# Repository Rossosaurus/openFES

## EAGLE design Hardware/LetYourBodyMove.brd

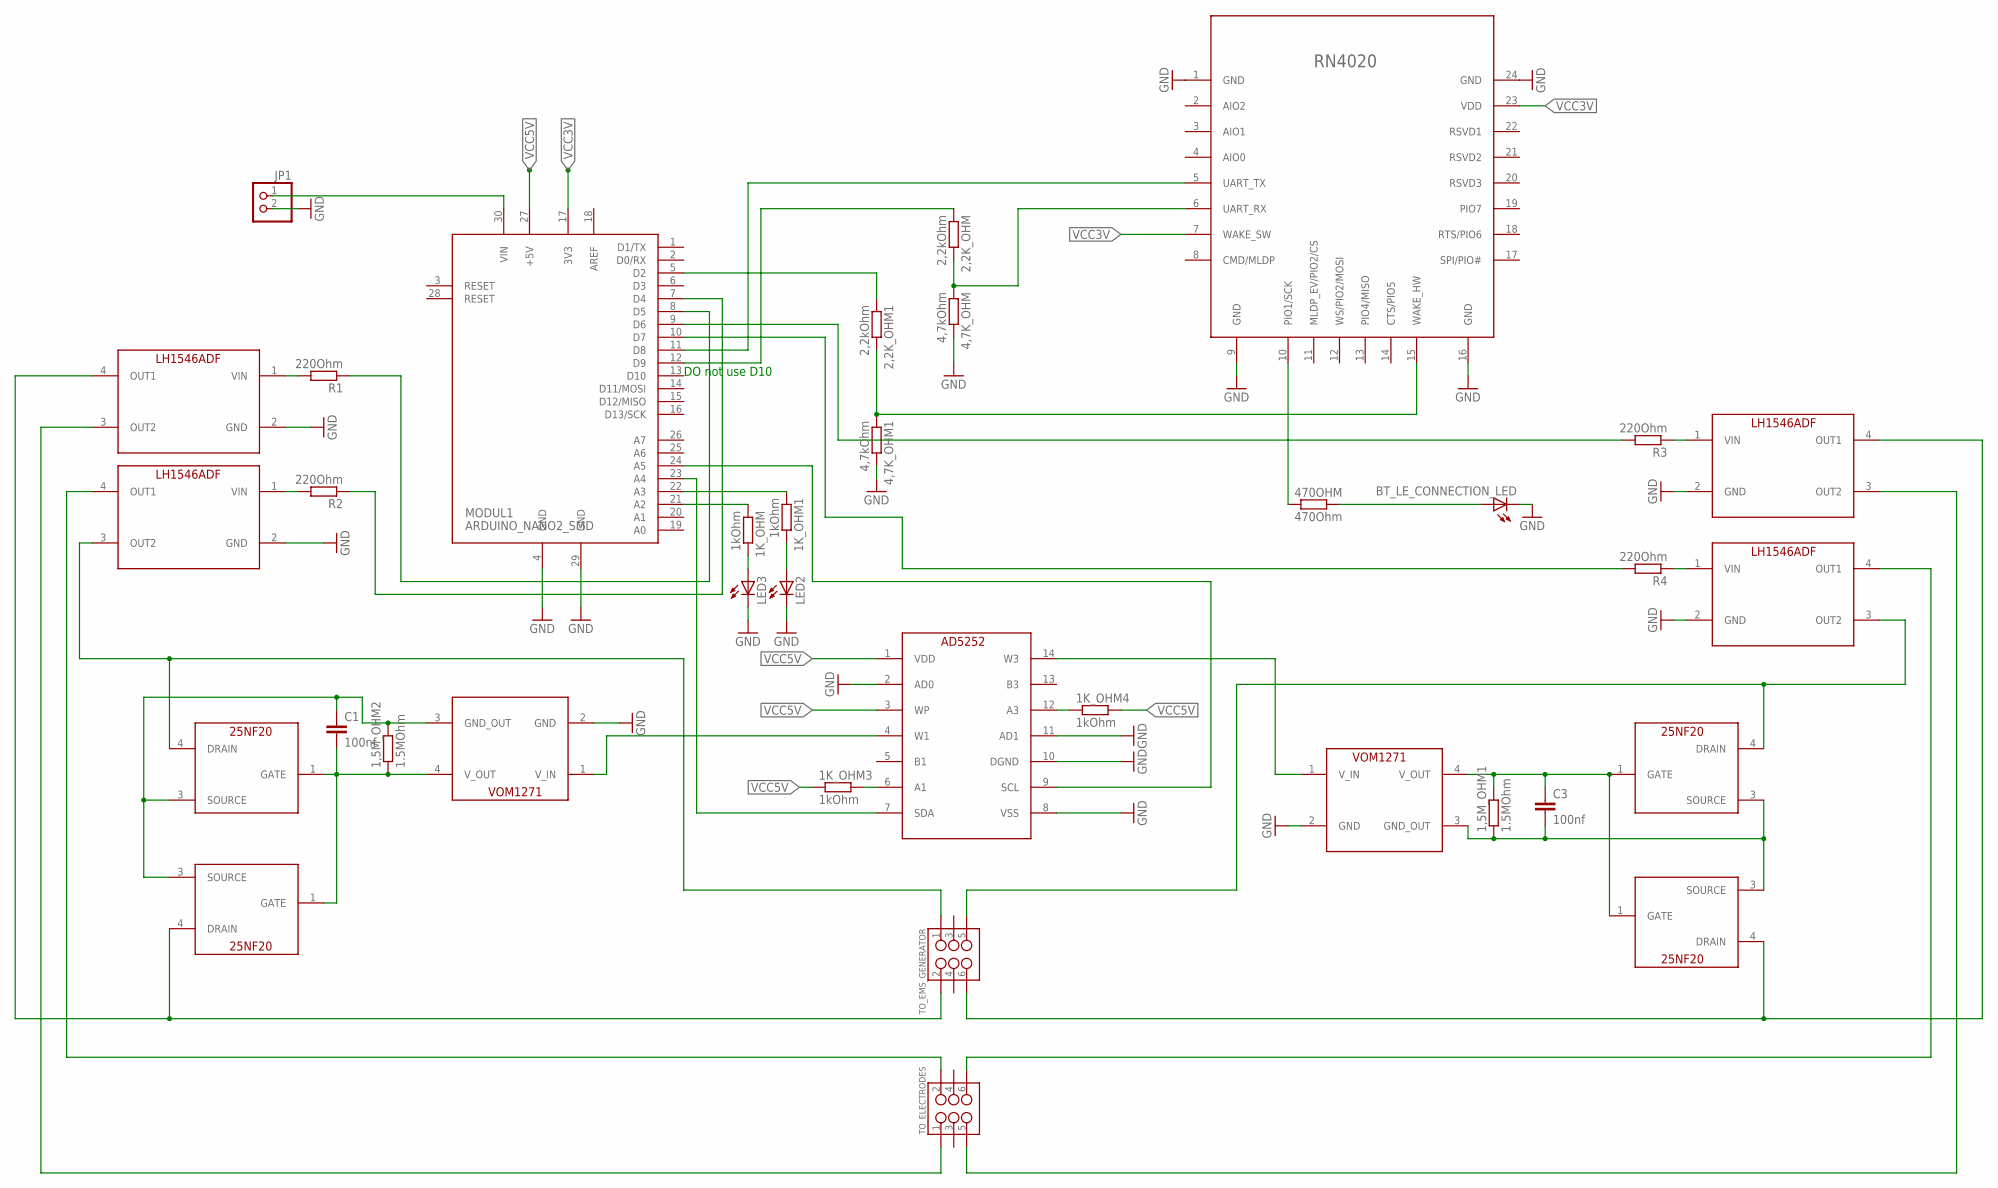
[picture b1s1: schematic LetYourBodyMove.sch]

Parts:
1,5M_OHM1, 1,5M_OHM2: 1.5MOhm; R0805
1K_OHM, 1K_OHM1, 1K_OHM3, 1K_OHM4: 1kOhm; R0805
2,2K_OHM, 2,2K_OHM1: 2,2kOhm; R0805
4,7K_OHM, 4,7K_OHM1: 4,7kOhm; R0805
470OHM: 470Ohm; R0805
BT_LE_CONNECTION_LED: LEDCHIPLED_0603; CHIPLED_0603
C1, C3: 100nf; 0805
JP1: PINHD-1X2; 1X02
LED2, LED3: LEDCHIPLED_0603; CHIPLED_0603
MODUL1: ARDUINO_NANO2_SMD
MOS01, MOS02, MOS03, MOS04: DEV; PACK
R1, R2, R3, R4: 220Ohm; R0805
TO_ELECTRODES: M03X2; RIGHT_ANGLED_SHROUED_2X06_6PIN
TO_EMS_GENERATOR: M03X2; RIGHT_ANGLED_SHROUED_2X06_6PIN
U$5: RN4020
U$6: AD5252; TSSOP
U$9, U$10: VOM1271; SOP04
U$11, U$12, U$13, U$14: LH1546ADF; DIP04-SMD

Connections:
AREF: MODUL1.18 (AREF)
GND: 4,7K_OHM.2, 4,7K_OHM1.2, BT_LE_CONNECTION_LED.C, JP1.2, LED2.C, LED3.C, MODUL1.4 (GND), MODUL1.29 (GND), U$5.1 (GND), U$5.9 (GND), U$5.16 (GND), U$5.24 (GND), U$6.2 (AD0), U$6.8 (VSS), U$6.10 (DGND), U$6.11 (AD1), U$9.2 (GND), U$10.2 (GND), U$11.2 (GND), U$12.2 (GND), U$13.2 (GND), U$14.2 (GND)
unnamed: U$6.4 (W1), U$9.1 (V_IN)
unnamed: 1K_OHM.1, MODUL1.21 (A2)
unnamed: MODUL1.23 (A4), U$6.7 (SDA)
unnamed: TO_ELECTRODES.6, U$14.4 (OUT1)
unnamed: 2,2K_OHM.2, 4,7K_OHM.1, U$5.6 (UART_RX)
unnamed: 2,2K_OHM.1, MODUL1.12 (D9)
unnamed: TO_ELECTRODES.1, U$11.3 (OUT2)
unnamed: 1,5M_OHM2.1, C1.2, MOS01.1 (GATE), MOS02.1 (GATE), U$9.4 (V_OUT)
unnamed: MODUL1.11 (D8), U$5.5 (UART_TX)
unnamed: MODUL1.24 (A5), U$6.9 (SCL)
unnamed: JP1.1, MODUL1.30 (VIN)
unnamed: R2.2, U$12.1 (VIN)
unnamed: TO_ELECTRODES.2, U$12.4 (OUT1)
unnamed: R1.2, U$11.1 (VIN)
unnamed: R3.1, U$13.1 (VIN)
unnamed: R4.1, U$14.1 (VIN)
unnamed: MODUL1.8 (D5), R1.1
unnamed: MODUL1.7 (D4), R2.1
unnamed: MODUL1.9 (D6), R3.2
unnamed: MODUL1.10 (D7), R4.2
unnamed: MOS01.4 (DRAIN), TO_EMS_GENERATOR.1, U$12.3 (OUT2)
unnamed: U$6.14 (W3), U$10.1 (V_IN)
unnamed: 1,5M_OHM1.2, C3.1, MOS03.1 (GATE), MOS04.1 (GATE), U$10.4 (V_OUT)
unnamed: 1,5M_OHM1.1, C3.2, MOS03.3 (SOURCE), MOS04.3 (SOURCE), U$10.3 (GND_OUT)
unnamed: 1K_OHM4.1, U$6.12 (A3)
unnamed: 1,5M_OHM2.2, C1.1, MOS01.3 (SOURCE), MOS02.3 (SOURCE), U$9.3 (GND_OUT)
unnamed: MOS03.4 (DRAIN), TO_EMS_GENERATOR.5, U$14.3 (OUT2)
unnamed: MOS02.4 (DRAIN), TO_EMS_GENERATOR.2, U$11.4 (OUT1)
unnamed: TO_ELECTRODES.5, U$13.3 (OUT2)
unnamed: MOS04.4 (DRAIN), TO_EMS_GENERATOR.6, U$13.4 (OUT1)
unnamed: 2,2K_OHM1.2, 4,7K_OHM1.1, U$5.15 (WAKE_HW)
unnamed: 1K_OHM3.2, U$6.6 (A1)
unnamed: 2,2K_OHM1.1, MODUL1.5 (D2)
unnamed: 470OHM.1, U$5.10 (PIO1/SCK)
unnamed: 470OHM.2, BT_LE_CONNECTION_LED.A
unnamed: 1K_OHM1.2, LED2.A
unnamed: 1K_OHM1.1, MODUL1.22 (A3)
unnamed: 1K_OHM.2, LED3.A
VCC3V: MODUL1.17 (3V3), U$5.7 (WAKE_SW), U$5.23 (VDD)
VCC5V: 1K_OHM3.1, 1K_OHM4.2, MODUL1.27 (+5V), U$6.1 (VDD), U$6.3 (WP)

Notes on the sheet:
DO not use D10

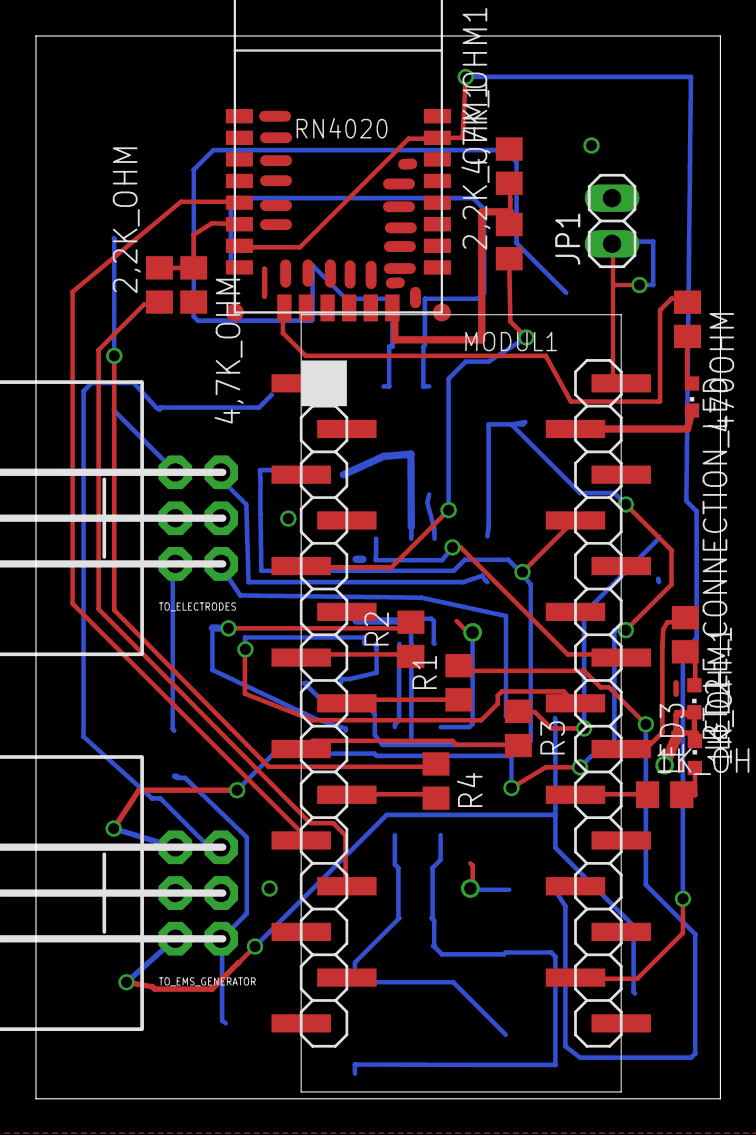
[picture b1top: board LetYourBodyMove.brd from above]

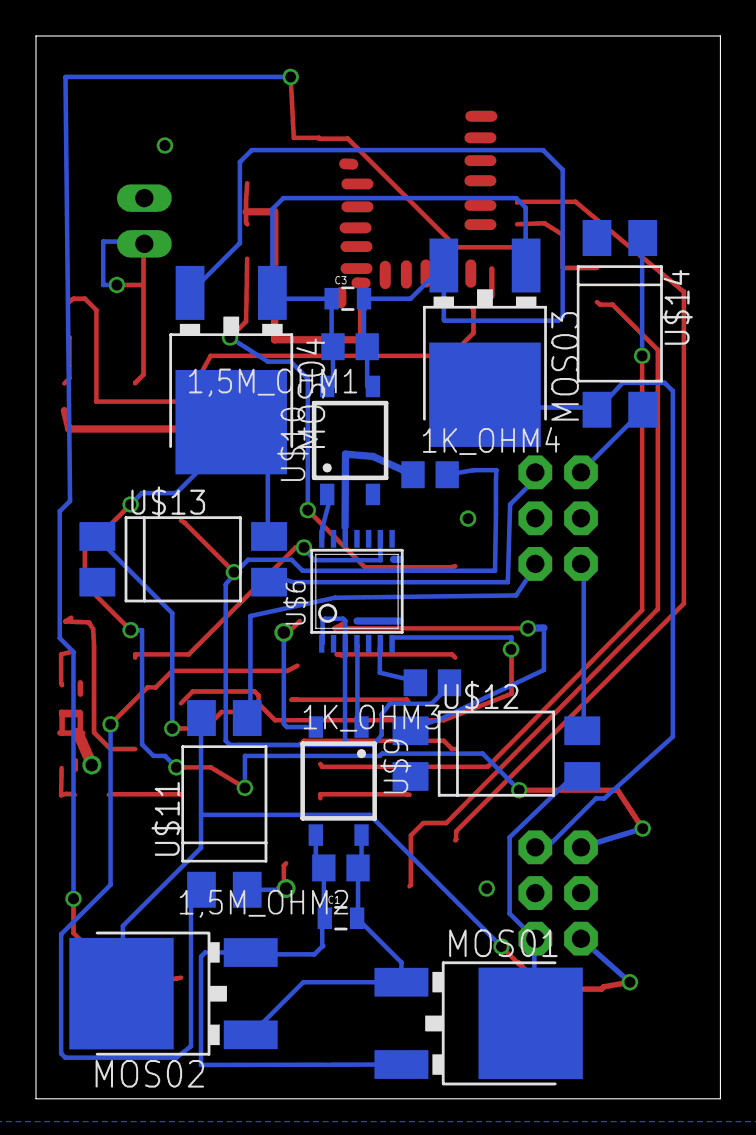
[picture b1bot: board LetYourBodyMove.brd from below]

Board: 2 copper layers, 38.0 x 59.0 mm, 36 parts (17 on the bottom side), 41 nets.

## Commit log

2025-02-22 Initial upload

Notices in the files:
parts and their libraries:
SparkFun-Passives: Licensing: Creative Commons ShareAlike 4.0 International - https://creativecommons.org/licenses/by-sa/4.0
